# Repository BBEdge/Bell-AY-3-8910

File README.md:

#### Bell-AY-3-8910

```
CPU 8085
GAL ATF16V  
DAC AY-3-8910
```

#### GLUE LOGIC
```
/** Inputs **/
Pin 1 = CLK;
Pin 2 = IOM;
Pin 3 = RD;
Pin 4 = WR;
Pin 5 = A14;
Pin 6 = A15;

/** Outputs **/
Pin 16 = RAM_CS;
Pin 17 = ROM_CS;
Pin 18 = BC1;
Pin 19 = BDIR;

/** IOM Logic **/
!BC1 = !A14 # !IOM;
!BDIR = WR # !IOM;
!ROM_CS = !A15 & !IOM;
!RAM_CS = A15 & !IOM;
```

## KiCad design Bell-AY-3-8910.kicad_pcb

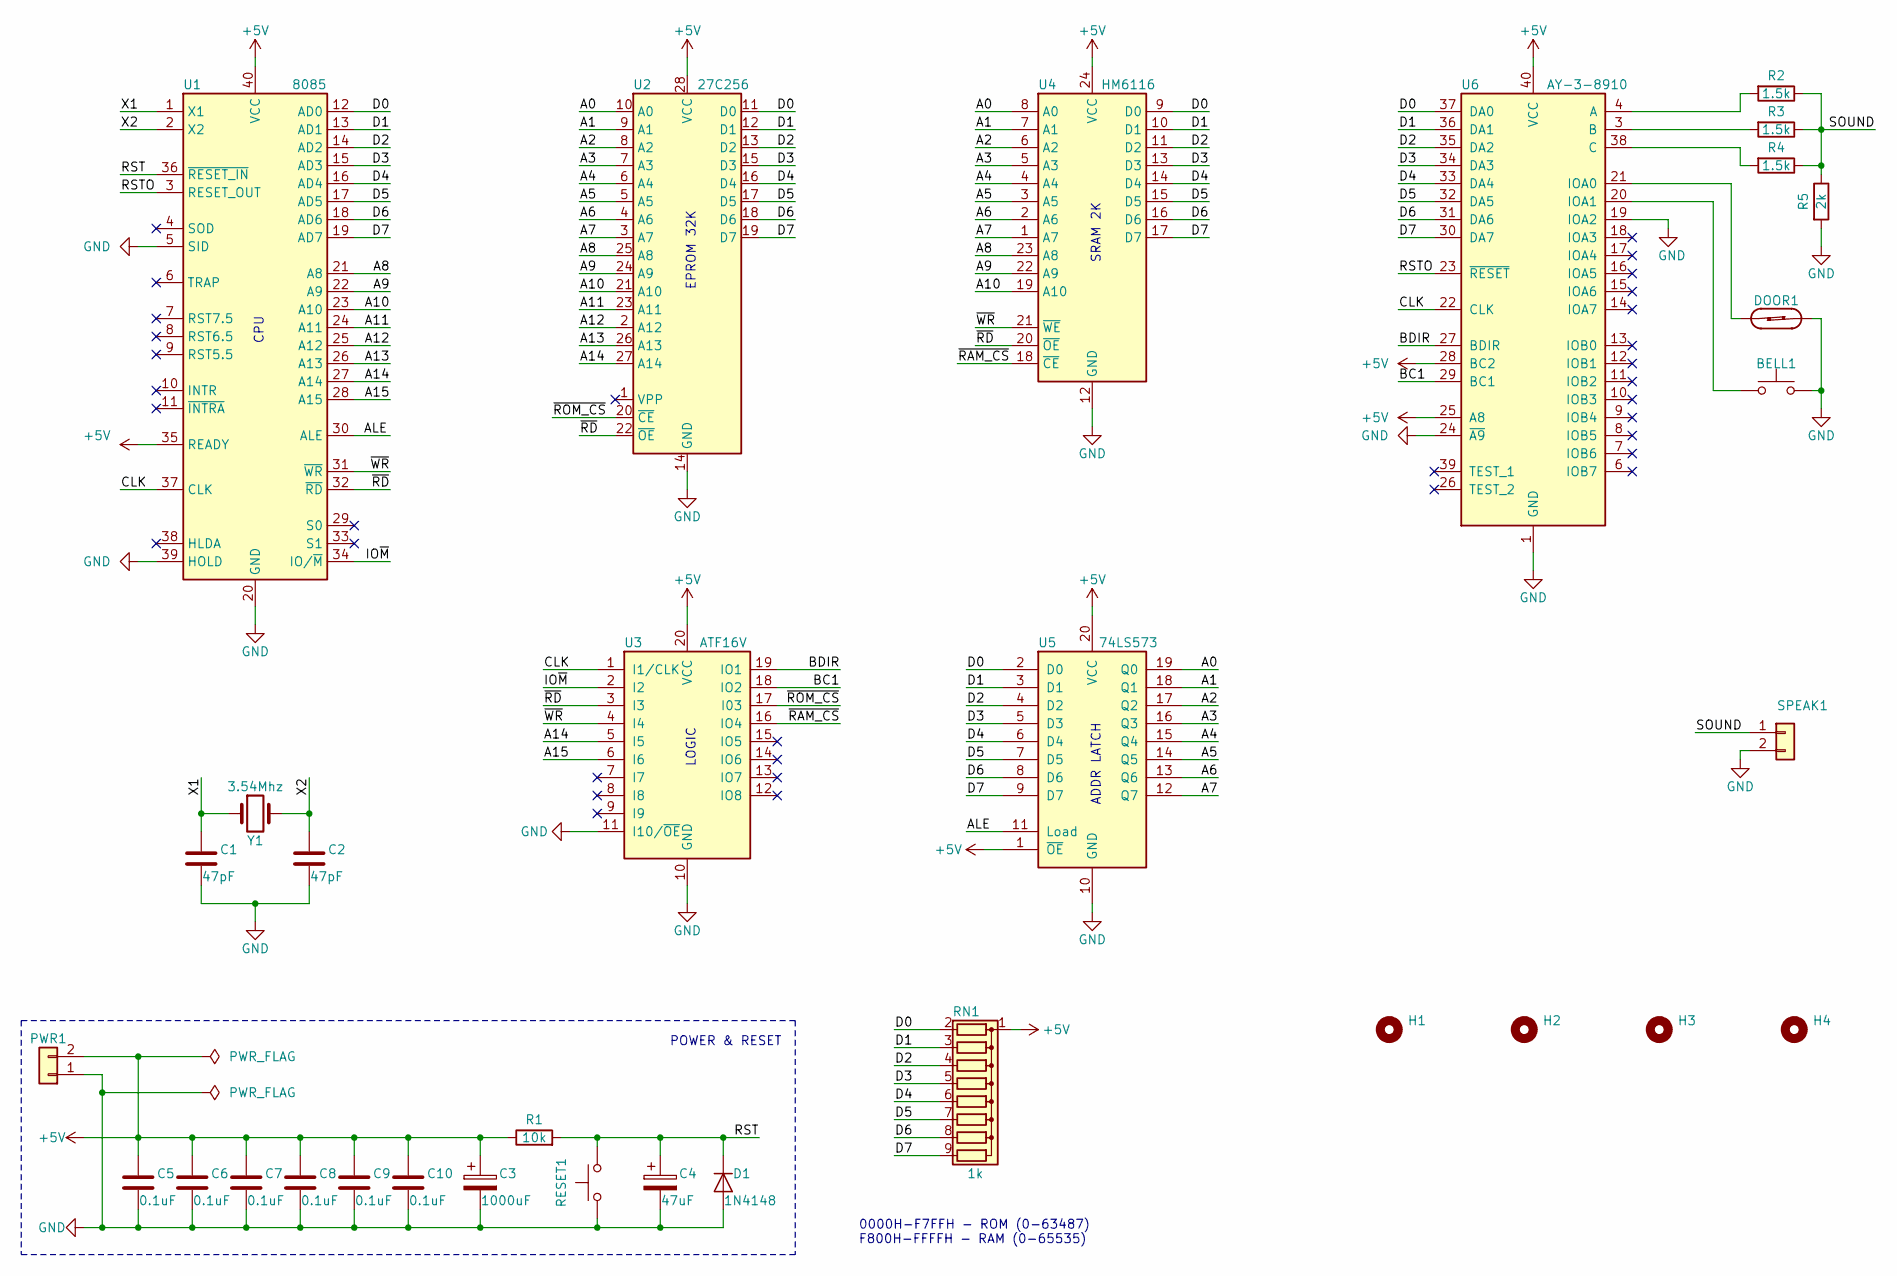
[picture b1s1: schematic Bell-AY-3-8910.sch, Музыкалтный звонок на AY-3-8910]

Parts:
BELL1: SW3; SW_PUSH_6mm
C1, C2: 47pF; C_Disc_D6.0mm_W2.5mm_P5.00mm
C3: 1000uF; CP_Radial_D8.0mm_P3.80mm
C4: 47uF; CP_Radial_D5.0mm_P2.50mm
C5, C6, C7, C8, C9, C10: 0.1uF; C_Disc_D6.0mm_W2.5mm_P5.00mm
D1: 1N4148; D_DO-35_SOD27_P7.62mm_Horizontal
DOOR1: SW2; JST_EH_B2B-EH-A_1x02_P2.50mm_Vertical
H1, H2, H3, H4: MountingHole; MountingHole_2mm
PWR1: J1; JST_EH_B2B-EH-A_1x02_P2.50mm_Vertical
R1: 10k; R_Axial_DIN0204_L3.6mm_D1.6mm_P7.62mm_Horizontal
R2, R3, R4: 1.5k; R_Axial_DIN0204_L3.6mm_D1.6mm_P7.62mm_Horizontal
R5: 2k; R_Axial_DIN0204_L3.6mm_D1.6mm_P7.62mm_Horizontal
RESET1: SW1; SW_Tactile_SPST_Angled_PTS645Vx39-2LFS
RN1: 1k; R_Array_SIP9
SPEAK1: J2; JST_EH_B2B-EH-A_1x02_P2.50mm_Vertical
U1: 8085; DIP-40_W15.24mm
U2: 27C256; DIP-28_W15.24mm_Socket
U3: ATF16V; DIP-20_W7.62mm
U4: HM6116; DIP-24_W15.24mm
U5: 74LS573; DIP-20_W7.62mm
U6: AY-3-8910; DIP-40_W15.24mm
Y1: 3.54Mhz; Crystal_HC49-U_Vertical

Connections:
+5V: C3.1, C5.1, C6.1, C7.1, C8.1, C9.1, C10.1, PWR1.2, R1.1, RN1.1 (common), U1.35 (READY), U1.40 (VCC), U2.28 (VCC), U3.20 (VCC), U4.24 (VCC), U5.1 (~OE), U5.20 (VCC), U6.25 (A8), U6.28 (BC2), U6.40 (VCC)
/A0: U2.10 (A0), U4.8 (A0), U5.19 (Q0)
/A1: U2.9 (A1), U4.7 (A1), U5.18 (Q1)
/A2: U2.8 (A2), U4.6 (A2), U5.17 (Q2)
/A3: U2.7 (A3), U4.5 (A3), U5.16 (Q3)
/A4: U2.6 (A4), U4.4 (A4), U5.15 (Q4)
/A5: U2.5 (A5), U4.3 (A5), U5.14 (Q5)
/A6: U2.4 (A6), U4.2 (A6), U5.13 (Q6)
/A7: U2.3 (A7), U4.1 (A7), U5.12 (Q7)
/A8: U1.21 (A8), U2.25 (A8), U4.23 (A8)
/A9: U1.22 (A9), U2.24 (A9), U4.22 (A9)
/A10: U1.23 (A10), U2.21 (A10), U4.19 (A10)
/A11: U1.24 (A11), U2.23 (A11)
/A12: U1.25 (A12), U2.2 (A12)
/A13: U1.26 (A13), U2.26 (A13)
/A14: U1.27 (A14), U2.27 (A14), U3.5 (I5)
/A15: U1.28 (A15), U3.6 (I6)
/ALE: U1.30 (ALE), U5.11 (Load)
/BC1: U3.18 (IO2), U6.29 (BC1)
/BDIR: U3.19 (IO1), U6.27 (BDIR)
/CLK: U1.37 (CLK), U3.1 (I1/CLK), U6.22 (CLK)
/D0: RN1.2 (R1), U1.12 (AD0), U2.11 (D0), U4.9 (D0), U5.2 (D0), U6.37 (DA0)
/D1: RN1.3 (R2), U1.13 (AD1), U2.12 (D1), U4.10 (D1), U5.3 (D1), U6.36 (DA1)
/D2: RN1.4 (R3), U1.14 (AD2), U2.13 (D2), U4.11 (D2), U5.4 (D2), U6.35 (DA2)
/D3: RN1.5 (R4), U1.15 (AD3), U2.15 (D3), U4.13 (D3), U5.5 (D3), U6.34 (DA3)
/D4: RN1.6 (R5), U1.16 (AD4), U2.16 (D4), U4.14 (D4), U5.6 (D4), U6.33 (DA4)
/D5: RN1.7 (R6), U1.17 (AD5), U2.17 (D5), U4.15 (D5), U5.7 (D5), U6.32 (DA5)
/D6: RN1.8 (R7), U1.18 (AD6), U2.18 (D6), U4.16 (D6), U5.8 (D6), U6.31 (DA6)
/D7: RN1.9 (R8), U1.19 (AD7), U2.19 (D7), U4.17 (D7), U5.9 (D7), U6.30 (DA7)
/IO~M: U1.34 (IO/~M~), U3.2 (I2)
/RST: C4.1, D1.1 (K), R1.2, RESET1.2, U1.36 (~RESET_IN~)
/RSTO: U1.3 (RESET_OUT), U6.23 (~RESET~)
/SOUND: R2.1, R3.1, R4.1, R5.1, SPEAK1.1
/X1: C1.1, U1.1 (X1), Y1.1
/X2: C2.1, U1.2 (X2), Y1.2
/~RAM_CS: U3.16 (IO4), U4.18 (~CE)
/~RD: U1.32 (~RD~), U2.22 (~OE), U3.3 (I3), U4.20 (~OE)
/~ROM_CS: U2.20 (~CE), U3.17 (I03)
/~WR: U1.31 (~WR~), U3.4 (I4), U4.21 (~WE)
GND: BELL1.2, C1.2, C2.2, C3.2, C4.2, C5.2, C6.2, C7.2, C8.2, C9.2, C10.2, D1.2 (A), DOOR1.2, PWR1.1, R5.2, RESET1.1, SPEAK1.2, U1.5 (SID), U1.20 (GND), U1.39 (HOLD), U2.14 (GND), U3.10 (GND), U3.11 (I10/~OE~), U4.12 (GND), U5.10 (GND), U6.1 (GND), U6.19 (IOA2), U6.24 (~A9~)
unnamed: BELL1.1, U6.20 (IOA1)
unnamed: DOOR1.1, U6.21 (IOA0)
unnamed: R2.2, U6.4 (A)
unnamed: R3.2, U6.3 (B)
unnamed: R4.2, U6.38 (C)

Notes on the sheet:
ADDR LATCH
CPU
SRAM 2K
EPROM 32K
LOGIC
POWER & RESET
0000H-F7FFH - ROM (0-63487) F800H-FFFFH - RAM (0-65535)

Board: 2 copper layers, 33 parts (0 on the bottom side), 45 nets, no tracks yet.

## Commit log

2020-05-16 rev3
